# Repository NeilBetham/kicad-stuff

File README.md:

kicad-stuff
===========

This is my collection of KiCAD projects. I make no guarantee that they are good or will pass EMC. However most work to
my level of satisfaction.

I also have a lib from custom symbols and footprints but my hygine on labeling and naming is kinda shit so use at your
own risk there as well.

### Active Projects
- Davis Receiver - TM4C + CC1125, PoE powered wireless receiver for Davis Instruments ISS
- Sea LED - TM4C based, ethernet connected, DMX lighting controller for use with marine lighting
- Weir Controller - ESP32 + TI Phy, ethernet connected, pond pump / lighting controller
- Nixie Clock - ESP32 + RTC + Switcher, fully integrated IN-18 nixie clock
- USB C Ambient Light Sensor - Goal here is to build a small dongle to regulate display brightness based on ambient light

### Deep Freeze Projects
- Keyboard - TKL, many other good options at the moment so not much drive to finish this
- High Voltage Power Supply - Was just a test board to prove out the design for the nixie clock

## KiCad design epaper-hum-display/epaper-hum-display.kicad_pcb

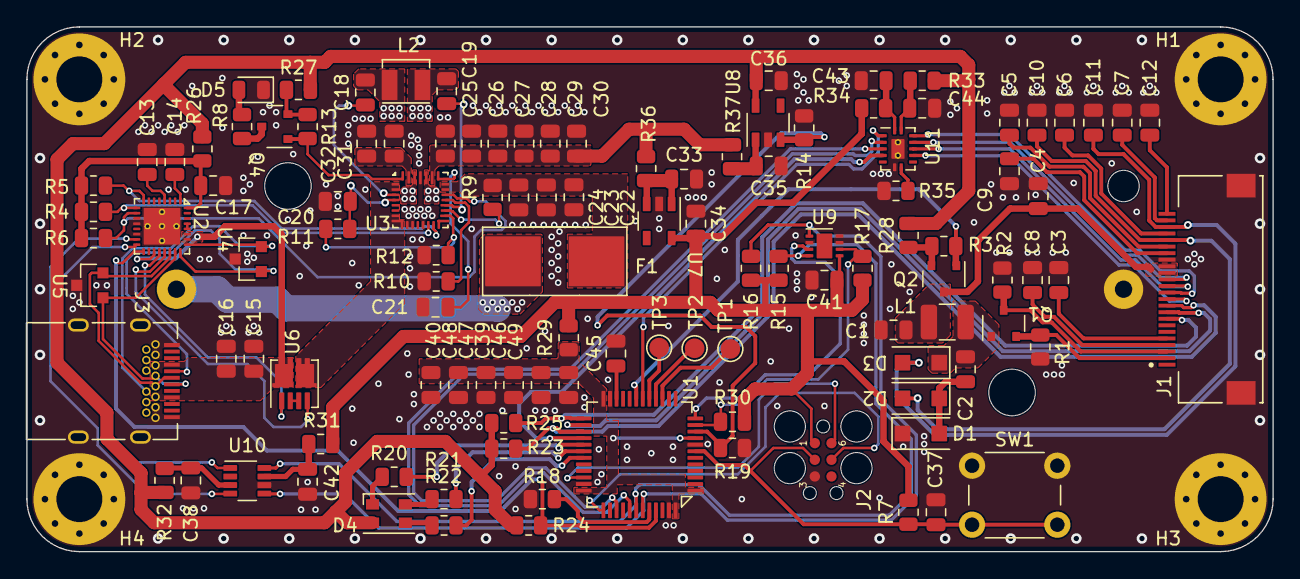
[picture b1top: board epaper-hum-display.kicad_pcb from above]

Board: 4 copper layers, 95.0 x 40.0 mm, 120 parts (1 on the bottom side), 93 nets.

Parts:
BT1: Battery_Cell; KEYSTONE-1043
C1, C2, C9: 4.7uF 50V; C_0805_2012Metric
C3, C5, C6, C7, C8, C10, C11, C12: 1uF 16V; C_0805_2012Metric
C4: 0.1 uF 16V; C_0805_2012Metric
C13, C14, C17, C23, C24, C26, C27, C28, C29, C30, C32, C34, C36, C40: 10uF 10V; C_0805_2012Metric
C15: 0.1uF 50V; C_0805_2012Metric
C16: 10uF 50V; C_0805_2012Metric
C18, C19: 0.047uF 25V; C_0805_2012Metric
C20: 4.7uF 25V; C_0805_2012Metric
C21: 1000pF 50V; C_0805_2012Metric
C22, C25, C31, C37, C38, C39, C41, C42, C43, C44, C46, C47, C48, C49: 0.1uF 10V; C_0805_2012Metric
C33, C35: 1uF 10V; C_0805_2012Metric
C45: 4.7uF 10V; C_0805_2012Metric
D1, D2, D3: MBR0530T1G; SOD-123W
D4: LED_RABG; LED_Cree-PLCC4_3.2x2.8mm_CCW
D5: BLUE; LED_0805_2012Metric
F1: Fuse; 01550900M
H1, H2, H3, H4: MountingHole_Pad; MountingHole_3.5mm_Pad_Via
J1: F31L-1A7H1-11024
J2: TC2030-SWD; TC2030-IDC-FP
J3: USB_C_Receptacle; Wurth_632723300011
L1: NLCV32T-680K-EF; L_1210_3225Metric
L2: SRP0315-1R0K; SRP0315
Q1: Si1308EDL; SOT-23-3
Q2, Q4: PMV65XP,215; SOT-23-3
R1, R3: 10K; R_0805_2012Metric
R2: 3; R_0805_2012Metric
R4, R5, R6, R15, R16, R17: 2.2k; R_0805_2012Metric
R7, R13, R14, R18, R19, R23, R24, R25, R30: 10k; R_0805_2012Metric
R8, R20, R21, R22: 500; R_0805_2012Metric
R9: 100; R_0805_2012Metric
R10: 3k 1%; R_0805_2012Metric
R11: 137k 1%; R_0805_2012Metric
R12: 2.2k 1%; R_0805_2012Metric
R26, R27, R28, R29, R31, R32, R33, R34, R35, R36, R37: 0; R_0805_2012Metric
SW1: B3F-1000; SW_PUSH_6mm
TP1, TP2, TP3: TestPoint; TestPoint_Pad_D1.5mm
U1: STM32U575CIT6Q; LQFP-48
U2: TPS25750S; VFQFN-32
U3: BQ25798; VFQFN-29
U4, U5: CDSOT23-0502B; SOT23-3L
U6: SISF00DN; PowerPAK 1212-8SCD Dual
U7: TPS7A2018PDBVR; SOT23-5
U8: TPS7A2033PDBVR; SOT23-5
U9: HDC3022; WSON-8
U10: TCA9416DDF; SOT-23-8
U11: TXU0104BQA; WQFN-14

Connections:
+1V8: C34.1, C41.1, J2.1 (VCC), R7.1, R15.1, R16.1, R17.1, R29.1, R30.1, R31.2, R34.2, U7.5 (OUT), U9.5 (VDD)
+3V3: C36.1, D4.2 (A), R23.1, R24.1, R25.1, R26.2, R27.1, R28.2, R32.1, R33.1, U8.5 (OUT)
/3V3_EN: R14.2, R19.1, U1.10 (PA0), U8.3 (EN)
/BATT_SCL: U2.16 (I2Cm_SCL), U10.1 (SCL_A)
/BATT_SDA: U2.15 (I2Cm_SDA), U10.4 (SDA_A)
/Battery/BQ_I2C_SCL: R4.2, U2.9 (I2Cs_SCL), U3.14 (SCL)
/Battery/BQ_I2C_SDA: R5.2, U2.8 (I2Cs_SDA), U3.15 (SDA)
/Battery/CC1: J3.A5 (CC1), U2.24 (CC1), U4.1
/Battery/CC2: J3.B5 (CC2), U2.25 (CC2), U4.2
/Battery/PD_CTRLR_3V3: C17.2, R4.1, R5.1, R6.1, R26.1, U2.32 (VIN_3V3)
/Battery/REGN: C20.1, R11.2, U3.5 (REGN)
/Battery/USB_N: J3.A7 (D-), J3.B7 (D-), U2.23 (GPIO5/USB_N), U5.1
/Battery/USB_P: J3.A6 (D+), J3.B6 (D+), U2.22 (GPIO4/USB_P), U5.2
/Battery/VBUS: C15.2, C16.2, J3.A4 (VBUS), J3.A9 (VBUS), J3.B4 (VBUS), J3.B9 (VBUS), U2.19 (VSYS), U2.26 (VBUS), U2.27 (VBUS), U6.7 (S1), U6.8 (S1)
/Battery/VSYS: C25.1, C26.1, C27.1, C28.1, C29.1, C30.1, R36.2, R37.2, U3.25 (SYS)
/Battery/~BQ_I2C_IRQ: R6.2, U2.10 (~I2Cs_IRQ), U3.21 (~INT)
/CDSTOP: TP2.1, U1.16 (PA6)
/CSLEEP: TP1.1, U1.15 (PA5)
/DISPLAY_BUSY: J1.9 (BUSY), U1.26 (PB13)
/DISPLAY_BUS_SEL: J1.8 (BS), R25.2, U1.25 (PB12)
/DISPLAY_CS: U1.18 (PB0), U11.2 (A1)
/DISPLAY_CS_S: J1.12 (CS), U11.13 (B1Y)
/DISPLAY_DATA_COMM_CTL: U1.28 (PB15), U11.5 (A4)
/DISPLAY_DATA_COMM_CTL_S: J1.11 (D/C), U11.10 (B4Y)
/DISPLAY_EN: Q2.1 (G), R3.1, U1.19 (PB1)
/DISPLAY_LVL_OE: R35.2, U11.8 (OE)
/DISPLAY_MOSI: U1.41 (PB5), U11.4 (A3)
/DISPLAY_MOSI_S: J1.14 (SDI), U11.12 (B2Y)
/DISPLAY_RESET: J1.10 (RST), R23.2, U1.27 (PB14)
/DISPLAY_SCLK: U1.39 (PB3), U11.3 (A2)
/DISPLAY_SCLK_S: J1.13 (SCLK), U11.11 (B3Y)
/E-Paper Display/EPAPER_3V3: C1.1, C4.1, J1.15 (VDDIO), J1.16 (VCI), L1.1, Q2.3 (D)
/E-Paper Display/GDR: J1.2 (GDR), Q1.2 (G), R1.2
/E-Paper Display/PREVGH: C10.1, D2.2 (A), J1.20 (VSH)
/E-Paper Display/PREVGL: C11.1, D3.2 (A), J1.22 (VSL)
/E-Paper Display/RESE: J1.3 (RESE), Q1.3 (S), R2.1
/HUM_ALERT: U1.12 (PA2), U9.3 (ALERT)
/HUM_RESET: R17.2, R30.2, U1.11 (PA1), U9.6 (~RESET)
/I2C_SCL: R15.2, U1.42 (PB6), U9.4 (SCL), U10.8 (SCL_B)
/I2C_SDA: R16.2, U1.43 (PB7), U9.1 (SDA), U10.5 (SDA_B)
/IND_B: R22.2, U1.31 (PA10)
/IND_G: R21.2, U1.30 (PA9)
/IND_R: R20.2, U1.29 (PA8)
/SRDSTOP: TP3.1, U1.17 (PA7)
/SWCLK: J2.5 (SWDCLK), U1.37 (PA14)
/SWDIO: J2.6 (SWDIO), U1.34 (PA13)
/nRESET: C37.1, J2.2 (nRESET), R7.2, SW1.2, U1.7 (NRST)
/~BATT_IRQ: R24.2, U1.45 (PB8), U2.17 (~I2Cm_IRQ)
GND: BT1.2 (-), C1.2, C3.2, C4.2, C5.2, C6.2, C7.2, C8.2, C9.2, C10.2, C11.2, C12.2, C13.2, C14.2, C15.1, C16.1, C17.1, C20.2, C21.2, C22.2, C23.2, C24.2, C25.2, C26.2, C27.2, C28.2, C29.2, C30.2, C31.2, C32.2, C33.2, C34.2, C35.2, C36.2, C37.2, C38.2, C39.2, C40.2, C41.2, C42.2, C43.2, C44.2, C45.1, C46.2, C47.2, C48.2, C49.2, D1.1 (K), D5.1 (K), H1.1, H2.1, H3.1, H4.1, J1.17 (VSS), J1.GND, J2.3 (GND), J3.A1 (GND), J3.A12 (GND), J3.B1 (GND), J3.B12 (GND), J3.S1 (SHIELD), R1.1, R2.2, R10.2, R12.1, R14.1, R18.2, R19.2, R35.1, SW1.1, U1.8 (VSSA), U1.23 (VSS), U1.35 (VSS), U1.47 (VSS), U2.11 (GND), U2.12 (GND), U2.14 (GND), U2.33 (GND), U3.10 (ACDRV2), U3.11 (ACDRV1), U3.13 (~CE), U3.27 (GND), U4.3, U5.3, U7.2 (GND), U8.2 (GND), U9.2 (ADDR), U9.7 (ADDR1), U9.8 (GND), U10.6 (GND), U11.7 (GND), U11.15 (GND)
unnamed: BT1.1 (+), F1.2
unnamed: C22.1, C23.1, C24.1, F1.1, R9.1, U3.22 (BAT), U3.23 (BAT)
unnamed: C2.1, D1.2 (A), D2.1 (K)
unnamed: C2.2, D3.1 (K), L1.2, Q1.1 (D)
unnamed: D4.3 (BK), R22.1
unnamed: D4.4 (GK), R21.1
unnamed: D4.1 (RK), R20.1
unnamed: D5.2 (A), R8.2
unnamed: C6.1, J1.21 (PREVGH)
unnamed: C7.1, J1.23 (PREVGL)
unnamed: C12.1, J1.24 (VCOM)
unnamed: C9.1, J1.18 (VDD)
unnamed: C3.1, J1.5 (VGH)
unnamed: C8.1, J1.4 (VGL)
unnamed: C5.1, J1.19 (VPP)
unnamed: Q2.2 (S), R3.2, R28.1
unnamed: Q4.3 (D), R8.1
unnamed: Q4.1 (G), R13.2, U3.1 (STAT)
unnamed: Q4.2 (S), R13.1, R27.2
unnamed: R18.1, U1.44 (PH3/BOOT0)
unnamed: C39.1, C40.1, C46.1, C47.1, C48.1, C49.1, R29.2, U1.1 (VBAT), U1.9 (VDDA), U1.24 (VDD), U1.36 (VDD), U1.48 (VDD)
unnamed: C45.2, U1.22 (VCAP)
unnamed: U2.21 (GATE_VBUS), U6.4 (G2)
unnamed: U2.20 (GATE_VSYS), U6.1 (G1)
unnamed: C13.1, U2.4 (LDO_1V5)
unnamed: C14.1, U2.1 (LDO_3V3)
unnamed: U2.28 (PP5V), U2.29 (PP5V)
unnamed: R9.2, U3.18 (BATP)
unnamed: C18.1, U3.4 (BTST1)
unnamed: C19.1, U3.19 (BTST2)
unnamed: R11.1, R12.2, U3.17 (ILIM_HIZ)
unnamed: C31.1, C32.1, U3.29 (PMID)
unnamed: R10.1, U3.20 (PROG)
unnamed: C21.1, U3.24 (SDRV)
unnamed: C18.2, L2.2, U3.28 (SW1)
unnamed: C19.2, L2.1, U3.26 (SW2)
unnamed: U3.2 (VBUS), U3.3 (VBUS), U3.8 (VAC2), U3.9 (VAC1), U6.5 (S2), U6.6 (S2)
unnamed: U6.2 (D), U6.3 (D)
unnamed: C33.1, R36.1, U7.1 (IN), U7.3 (EN)
unnamed: C35.1, R37.1, U8.1 (IN)
unnamed: C38.1, R32.2, U10.3 (VCCA)
unnamed: C42.1, R31.1, U10.7 (VCCB)
unnamed: C43.1, R34.1, U11.1 (VCCA)
unnamed: C44.1, R33.2, U11.14 (VCCB)

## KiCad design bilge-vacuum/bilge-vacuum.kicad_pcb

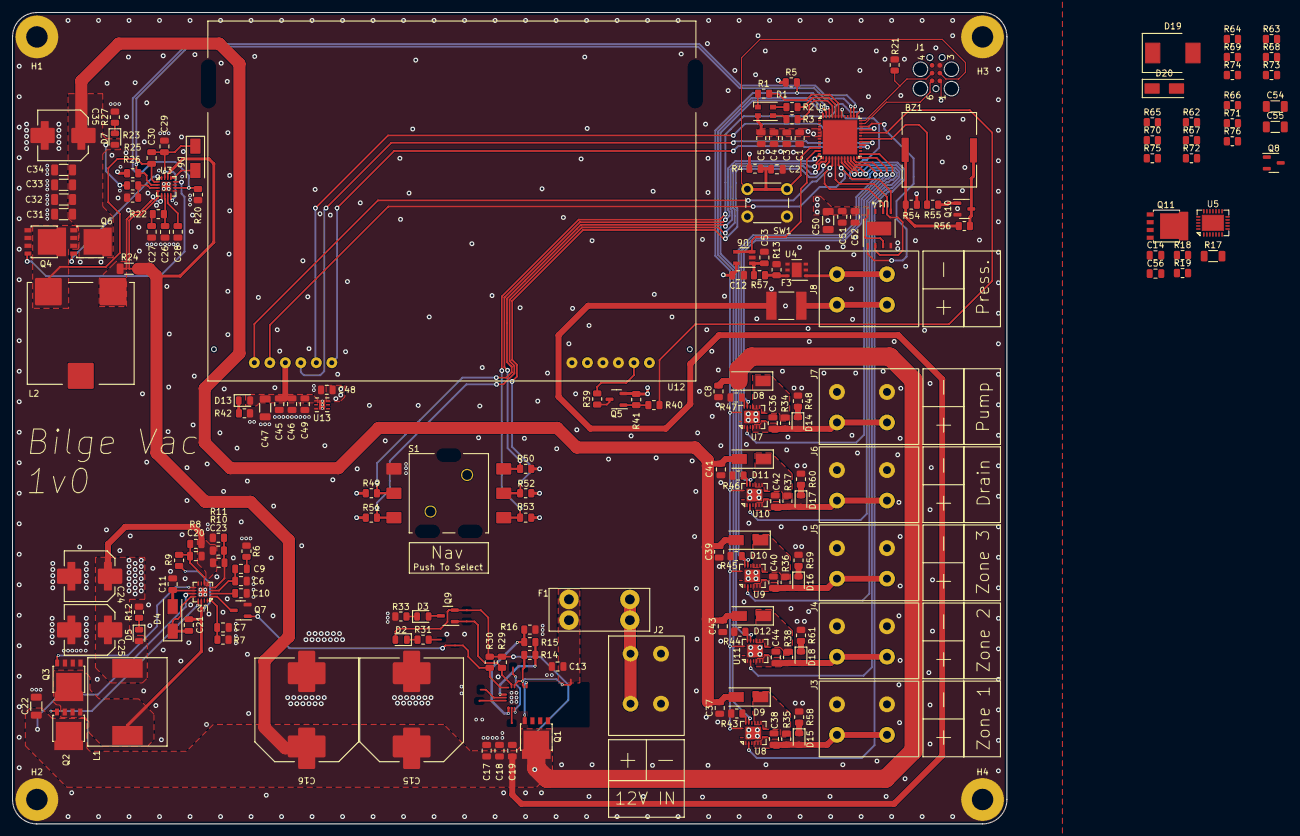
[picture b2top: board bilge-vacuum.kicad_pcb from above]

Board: 4 copper layers, 163.0 x 133.0 mm, 194 parts (0 on the bottom side), 113 nets.

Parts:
BZ1: PKLCS1212E40A1-R1
C1, C2, C3, C7, C8, C10, C12, C13, C14, C21, C28, C30, C36, C37, C38, C39, C40, C41, C42, C43, C44, C45, C52, C53, C56: 0.1uF 50V; C_0805_2012Metric
C4, C46, C48, C49, C51: 1uF 25V; C_0805_2012Metric
C5, C11, C17, C18, C19, C29: 4.7uF 50V; C_0805_2012Metric
C6: 330pF 25V; C_0805_2012Metric
C9: 2200pF 25V; C_0805_2012Metric
C15, C16: EEE-FK1H102AV; Panasonic - J - Vibe
C20: 0.047uF 25V; C_0805_2012Metric
C22, C31, C32, C33, C34, C47, C50, C54, C55: 10uF 50V; C_1206_3216Metric
C23: 47pF 10V; C_0805_2012Metric
C24, C25: EEE-FK1A331AV; Panasonic - F - Vibe
C26: 220pF 25V; C_0805_2012Metric
C27: 15000pF 25V; C_0805_2012Metric
C35: EEEFT1H221GV; Panasonic - F - Vibe
D1: LED_RABG; LED_Cree-PLCC4_3.2x2.8mm_CCW
D2, D5, D7, D13, D14, D15, D16, D17, D18: GREEN; LED_0805_2012Metric
D3: RED; LED_0805_2012Metric
D4, D6, D8, D9, D10, D11, D12, D20: B260AQ-13-F; SMA
D19: 5.0SMDJ18CA; DO-214AB
F1: Fuse; Keystone-3568
F3: Polyfuse; SMD_2016
H1, H2, H3, H4: MountingHole_Pad; MountingHole_3.5mm_Pad
J1: TC2030-SWD; TC2030-IDC-FP
J2, J3, J4, J5, J6, J7, J8: Screw_Terminal_01x02; 2604-1102
L1: SRP1265A-R68M; SRP1265A
L2: B82559B6682A016; TDK-ERU-16
Q1, Q2, Q3, Q4, Q6, Q11: PSMN014-80YL; LFPAK56
Q5: PMV65XP,215; SOT-23-3
Q7, Q10: Q_NMOS_GSD; SOT-23-3
Q8, Q9: Q_PMOS_GSD; SOT-23-3
R1, R2, R3, R12, R42: 499; R_0805_2012Metric
R4, R5, R20, R23, R27, R29, R30, R41, R48, R49, R50, R51, R52, R53, R58, R59, R60, R61, R62, R63, R64, R65, R66, R67, R68, R69, R70, R71, R72, R73, R74, R75, R76: 10k 1%; R_0805_2012Metric
R6, R18, R34, R35, R36, R37, R38: 15k; R_0805_2012Metric
R7: 82.5k; R_0805_2012Metric
R8: 30.1k; R_0805_2012Metric
R9: 3.01k; R_0805_2012Metric
R10: 154k 1%; R_0805_2012Metric
R11: 48.7k 1%; R_0805_2012Metric
R13: 100 1%; R_0805_2012Metric
R14: 21.5k 1%; R_0805_2012Metric
R15: 1.1k 1%; R_0805_2012Metric
R16: 2k 1%; R_0805_2012Metric
R17: 3m 1% 1/2W; R_1206_3216Metric
R19: 2k; R_0805_2012Metric
R21: NP; R_0805_2012Metric
R22: 8.87k 1%; R_0805_2012Metric
R24: 8m 1%; R_1206_3216Metric
R25: 232k 1%; R_0805_2012Metric
R26: 12.1k 1%; R_0805_2012Metric
R31, R33, R43, R44, R45, R46: 5k 1%; R_0805_2012Metric
R39, R57: 0; R_0805_2012Metric
R40, R54, R55: 10; R_0805_2012Metric
R47: 1.2k 1%; R_0805_2012Metric
R56: 1k; R_0805_2012Metric
S1: JS5208
SW1: B3F-1000; SW_PUSH_6mm
U1: STM32G0B1CEU6; UFQFPN-48
U2: LTC3851; QFN-16
U3: LTC3786; QFN-16
U4: MAX14626; TDFN-6
U5: LTC4229; WFQFN-24
U6: LMV321; SOT23-5
U7, U8, U9, U10, U11: TPS27S100A; WQFN-16
U12: NHD-C12864A1Z-FSW-FBW-HTT
U13: ADP151; CP_6_3_ADI
U14: FM25V20A; WDFN-8

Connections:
+3V0: C45.1, C46.1, C47.1, C49.1, D13.2 (A), U12.3 (VDD), U13.1 (VOUT)
+3V3: C1.1, C3.1, C4.1, C5.1, C12.2, C20.2, C23.2, C24.1, C25.1, C48.1, C50.1, C51.1, C52.1, D1.2 (A), D5.2 (A), J1.1 (VCC), L1.2, Q5.2 (S), R4.1, R5.1, R8.2, R10.1, R23.2, R41.2, R49.1, R50.1, R51.1, R52.1, R53.1, R54.1, R72.2, R73.2, R74.2, R75.2, R76.2, U1.4 (VBAT), U1.5 (VREF+), U1.6 (VDD/VDDA), U2.5 (SENSE_N), U6.5 (V+), U13.6 (VIN), U14.3 (~WP), U14.8 (VDD)
+12V: C8.2, C15.1, C16.1, C17.1, C18.1, C19.1, C22.1, C54.1, C55.1, D8.2 (A), D20.1 (K), F3.1, Q1.1 (S), Q1.2 (S), Q1.3 (S), Q2.5 (D), Q8.2 (S), Q9.2 (S), R18.1, R24.1, R29.2, R30.2, U2.11 (VIN), U3.4 (SENSE+), U3.14 (VBIAS), U5.21 (OUT)
+24V: C31.1, C32.1, C33.1, C34.1, C35.1, C37.2, C39.2, C41.2, C43.2, D7.2 (A), D9.2 (A), D10.2 (A), D11.2 (A), D12.2 (A), Q6.5 (D), R25.1
/Display/BL_ENABLE: R40.1, U1.32 (PA10)
/Display/CS: U1.28 (PA8), U12.6 (~CS)
/Display/MOSI: U1.18 (PA7), U12.2 (SI), U14.5 (SI)
/Display/REG: U1.29 (PA9), U12.4 (A0)
/Display/RESET: U1.33 (PA11), U12.5 (~RESET)
/Display/SCLK: U1.16 (PA5), U12.1 (SCL), U14.6 (SCLK)
/FRAM/CS: U1.34 (PA12), U14.1 (~CS)
/FRAM/MISO: U1.17 (PA6), U14.2 (SO)
/Main uC/24V_ENABLE: R20.2, U1.38 (PD0), U3.10 (RUN)
/Main uC/24V_PGOOD: R23.1, U1.39 (PD1), U3.2 (PGOOD)
/Main uC/BUZZER_DRIVE: R55.1, U1.30 (PC6)
/Main uC/DISPLAY_3V0_ENABLE: U1.31 (PC7), U13.4 (EN)
/Main uC/IND_B: R3.2, U1.45 (PB6)
/Main uC/IND_G: R2.2, U1.44 (PB5)
/Main uC/IND_R: R1.2, U1.43 (PB4)
/Main uC/NAV_A: R50.2, S1.4 (A), U1.12 (PA1)
/Main uC/NAV_B: R49.2, S1.2 (B), U1.13 (PA2)
/Main uC/NAV_C: R53.2, S1.6 (C), U1.37 (PA15)
/Main uC/NAV_D: R52.2, S1.5 (D), U1.15 (PA4)
/Main uC/NAV_SEL: R51.2, S1.3 (SEL), U1.14 (PA3)
/Main uC/PRESSURE_ADC: U1.11 (PA0), U6.3 (-), U6.4
/Main uC/SWDCLK: J1.5 (SWDCLK), R21.1, U1.36 (PA14-BOOT0)
/Main uC/SWDIO: J1.6 (SWDIO), U1.35 (PA13)
/Main uC/nRESET: C2.1, J1.2 (nRESET), R4.2, SW1.2, U1.10 (PF2-NRST)
/Output Control/PUMP_DIAG: R62.1, U1.24 (PB12), U7.14 (DIAG_EN)
/Output Control/PUMP_EN: R67.1, U1.25 (PB13), U7.3 (EN)
/Output Control/PUMP_FLT: R5.2, R72.1, R73.1, R74.1, R75.1, R76.1, U1.46 (PB7), U7.16 (~FLT), U8.16 (~FLT), U9.16 (~FLT), U10.16 (~FLT), U11.16 (~FLT)
/Output Control/Pump Switch/CURRENT_LIMIT: R47.1, U7.15 (ILIM)
/Output Control/Pump Switch/OUT: C36.2, D14.2 (A), J7.1, R34.2, U7.5 (OUT), U7.6 (OUT), U7.7 (OUT), U7.8 (OUT)
/Output Control/SOL_1_DIAG: R63.1, U1.47 (PB8), U8.14 (DIAG_EN)
/Output Control/SOL_1_EN: R68.1, U1.19 (PB0), U8.3 (EN)
/Output Control/SOL_2_DIAG: R66.1, U1.48 (PB9), U11.14 (DIAG_EN)
/Output Control/SOL_2_EN: R71.1, U1.20 (PB1), U11.3 (EN)
/Output Control/SOL_3_DIAG: R64.1, U1.22 (PB10), U9.14 (DIAG_EN)
/Output Control/SOL_3_EN: R69.1, U1.21 (PB2), U9.3 (EN)
/Output Control/SOL_4_DIAG: R65.1, U1.23 (PB11), U10.14 (DIAG_EN)
/Output Control/SOL_4_EN: R70.1, U1.42 (PB3), U10.3 (EN)
/Output Control/Solenoid 1/CURRENT_LIMIT: R43.2, U8.15 (ILIM)
/Output Control/Solenoid 1/OUT: C38.2, D15.2 (A), J3.1, R35.2, U8.5 (OUT), U8.6 (OUT), U8.7 (OUT), U8.8 (OUT)
/Output Control/Solenoid 2/CURRENT_LIMIT: R44.2, U11.15 (ILIM)
/Output Control/Solenoid 2/OUT: C44.2, D18.2 (A), J4.1, R38.2, U11.5 (OUT), U11.6 (OUT), U11.7 (OUT), U11.8 (OUT)
/Output Control/Solenoid 3/CURRENT_LIMIT: R45.2, U9.15 (ILIM)
/Output Control/Solenoid 3/OUT: C40.2, D16.2 (A), J5.1, R36.2, U9.5 (OUT), U9.6 (OUT), U9.7 (OUT), U9.8 (OUT)
/Output Control/Solenoid 4/CURRENT_LIMIT: R46.2, U10.15 (ILIM)
/Output Control/Solenoid 4/OUT: C42.2, D17.2 (A), J6.1, R37.2, U10.5 (OUT), U10.6 (OUT), U10.7 (OUT), U10.8 (OUT)
/Power/3.3V Buck/BUCK_BG: Q3.4 (G), U2.9 (BG)
/Power/3.3V Buck/BUCK_TG: Q2.4 (G), U2.13 (TG)
/Power/3V3_ENABLE: Q7.3 (D), U2.1 (RUN)
/Power/24V Boost/24V_INTVCC: C29.2, D6.2 (A), U3.8 (PLLIN/MODE), U3.13 (INTVcc)
/Power/24V Boost/BOOST_BG: Q4.4 (G), U3.12 (BG)
/Power/24V Boost/BOOST_TG: Q6.4 (G), U3.16 (TG)
/Power/Input Protection/DIODE_GATE: Q11.4 (G), U5.24 (DGATE)
/Power/Input Protection/FOLDBACK_SENSE: R18.2, R19.1, U5.20 (FB)
/Power/Input Protection/HOTSWAP_GATE: Q1.4 (G), U5.22 (HGATE)
/Power/Input Protection/OVERVOLT_SENSE: R15.1, R16.2, U5.13 (OV)
/Power/Input Protection/SENSE_N: Q1.5 (D), Q11.5 (D), R17.1, R17.2, U5.2 (SENSE_N), U5.3 (SENSE_P), U5.5 (DSNS)
/Power/Input Protection/UNDERVOLT_SENSE: R14.1, R15.2, U5.12 (UV)
/Power/Input Protection/VIN: C13.1, D19.2 (A2), F1.1, F1.2, J2.1, Q11.1 (S), Q11.2 (S), Q11.3 (S), R14.2, U5.1 (DSRC), U5.4 (IN)
/Power/Input Protection/~FAULT: Q9.1 (G), R29.1, U5.18 (~FAULT)
/Power/Input Protection/~PGOOD: Q7.1 (G), Q8.1 (G), R30.1, U5.19 (~PWRGD)
GND: C1.2, C2.2, C3.2, C4.2, C5.2, C6.1, C7.1, C8.1, C10.1, C11.2, C12.1, C13.2, C14.2, C15.2, C16.2, C17.2, C18.2, C19.2, C22.2, C24.2, C25.2, C26.1, C27.1, C28.1, C29.1, C31.2, C32.2, C33.2, C34.2, C35.2, C36.1, C37.1, C38.1, C39.1, C40.1, C41.1, C42.1, C43.1, C44.1, C45.2, C46.2, C47.2, C48.2, C49.2, C50.2, C51.2, C52.2, C53.1, C54.2, C55.2, C56.2, D19.1 (A1), D20.2 (A), H1.1, H2.1, H3.1, H4.1, J1.3 (GND), J2.2, J3.2, J4.2, J5.2, J6.2, J7.2, Q3.1 (S), Q3.2 (S), Q3.3 (S), Q4.1 (S), Q4.2 (S), Q4.3 (S), Q7.2 (S), Q10.2 (S), R6.1, R7.1, R11.2, R12.2, R13.1, R16.1, R19.2, R20.1, R21.2, R26.1, R27.2, R31.2, R33.2, R42.2, R43.1, R44.1, R45.1, R46.1, R47.2, R48.2, R58.2, R59.2, R60.2, R61.2, R62.2, R63.2, R64.2, R65.2, R66.2, R67.2, R68.2, R69.2, R70.2, R71.2, S1.1 (COM), SW1.1, U1.7 (VSS/VSSA), U1.49 (VSS), U2.8 (GND), U2.17 (GND), U3.9 (FREQ), U3.11 (GND), U3.17 (GND), U4.2 (GND), U4.3 (GND), U4.4 (GND), U4.5 (GND), U4.7 (GND), U5.7 (GND), U5.11 (~EN), U5.14 (DCFG), U5.15 (DOFF), U5.25 (GND), U6.2 (V-), U7.2 (GND), U7.17 (GND), U8.2 (GND), U8.17 (GND), U9.2 (GND), U9.17 (GND), U10.2 (GND), U10.17 (GND), U11.2 (GND), U11.17 (GND), U12.7 (VSS), U12.9 (HEATER_GND), U12.10 (LED_GND), U13.3 (GND), U13.7 (GND), U14.4 (VSS)
unnamed: BZ1.2 (+), Q10.3 (D), R56.1
unnamed: BZ1.1 (-), R54.2, R56.2
unnamed: C9.1, R6.2
unnamed: C27.2, R22.1
unnamed: D1.3 (BK), R3.1
unnamed: D1.4 (GK), R2.1
unnamed: D1.1 (RK), R1.1
unnamed: D2.2 (A), Q8.3 (D)
unnamed: D2.1 (K), R31.1
unnamed: D3.2 (A), Q9.3 (D)
unnamed: D3.1 (K), R33.1
unnamed: C11.1, D4.2 (A), U2.10 (INTVCC)
unnamed: C21.1, D4.1 (K), U2.12 (BOOST)
unnamed: D5.1 (K), R12.1
unnamed: C30.1, D6.1 (K), U3.15 (BOOST)
unnamed: D7.1 (K), R27.1
unnamed: D8.1 (K), R34.1, U7.9 (IN), U7.10 (IN), U7.11 (IN), U7.12 (IN)
unnamed: D9.1 (K), R35.1, U8.9 (IN), U8.10 (IN), U8.11 (IN), U8.12 (IN)
unnamed: D10.1 (K), R36.1, U9.9 (IN), U9.10 (IN), U9.11 (IN), U9.12 (IN)
unnamed: D11.1 (K), R37.1, U10.9 (IN), U10.10 (IN), U10.11 (IN), U10.12 (IN)
unnamed: D12.1 (K), R38.1, U11.9 (IN), U11.10 (IN), U11.11 (IN), U11.12 (IN)
unnamed: D13.1 (K), R42.1
unnamed: D14.1 (K), R48.1
unnamed: D15.1 (K), R58.1
unnamed: D16.1 (K), R59.1
unnamed: D17.1 (K), R60.1
unnamed: D18.1 (K), R61.1
unnamed: F3.2, J8.1
unnamed: J8.2, U4.1 (IN)
unnamed: C21.2, L1.1, Q2.1 (S), Q2.2 (S), Q2.3 (S), Q3.5 (D), R9.1, U2.14 (SW)
unnamed: C30.2, L2.2, Q4.5 (D), Q6.1 (S), Q6.2 (S), Q6.3 (S), U3.1 (SW)
unnamed: Q5.3 (D), R39.2
unnamed: Q5.1 (G), R40.2, R41.1
unnamed: Q10.1 (G), R55.2
unnamed: C23.1, R10.2, R11.1, U2.4 (FB)
unnamed: C7.2, R7.2, U2.16 (FREQ/PLLFLTR)
unnamed: C6.2, C9.2, U2.3 (ITH)
unnamed: C20.1, R8.1, R9.2, U2.6 (SENSE_P)
unnamed: C10.2, U2.2 (TK/SS)
unnamed: C26.2, R22.2, U3.6 (ITH)
unnamed: L2.1, R24.2, U3.5 (SENSE-)
unnamed: C28.2, U3.7 (SS)
unnamed: R25.2, R26.2, U3.3 (VFB)
unnamed: R13.2, R57.2, U4.6 (OUT)
unnamed: C56.1, U5.6 (INTVcc), U5.8 (DTMR)
unnamed: C14.1, U5.10 (FTMR)
unnamed: C53.2, R57.1, U6.1 (+)
unnamed: R39.1, U12.11 (LED_3V3)

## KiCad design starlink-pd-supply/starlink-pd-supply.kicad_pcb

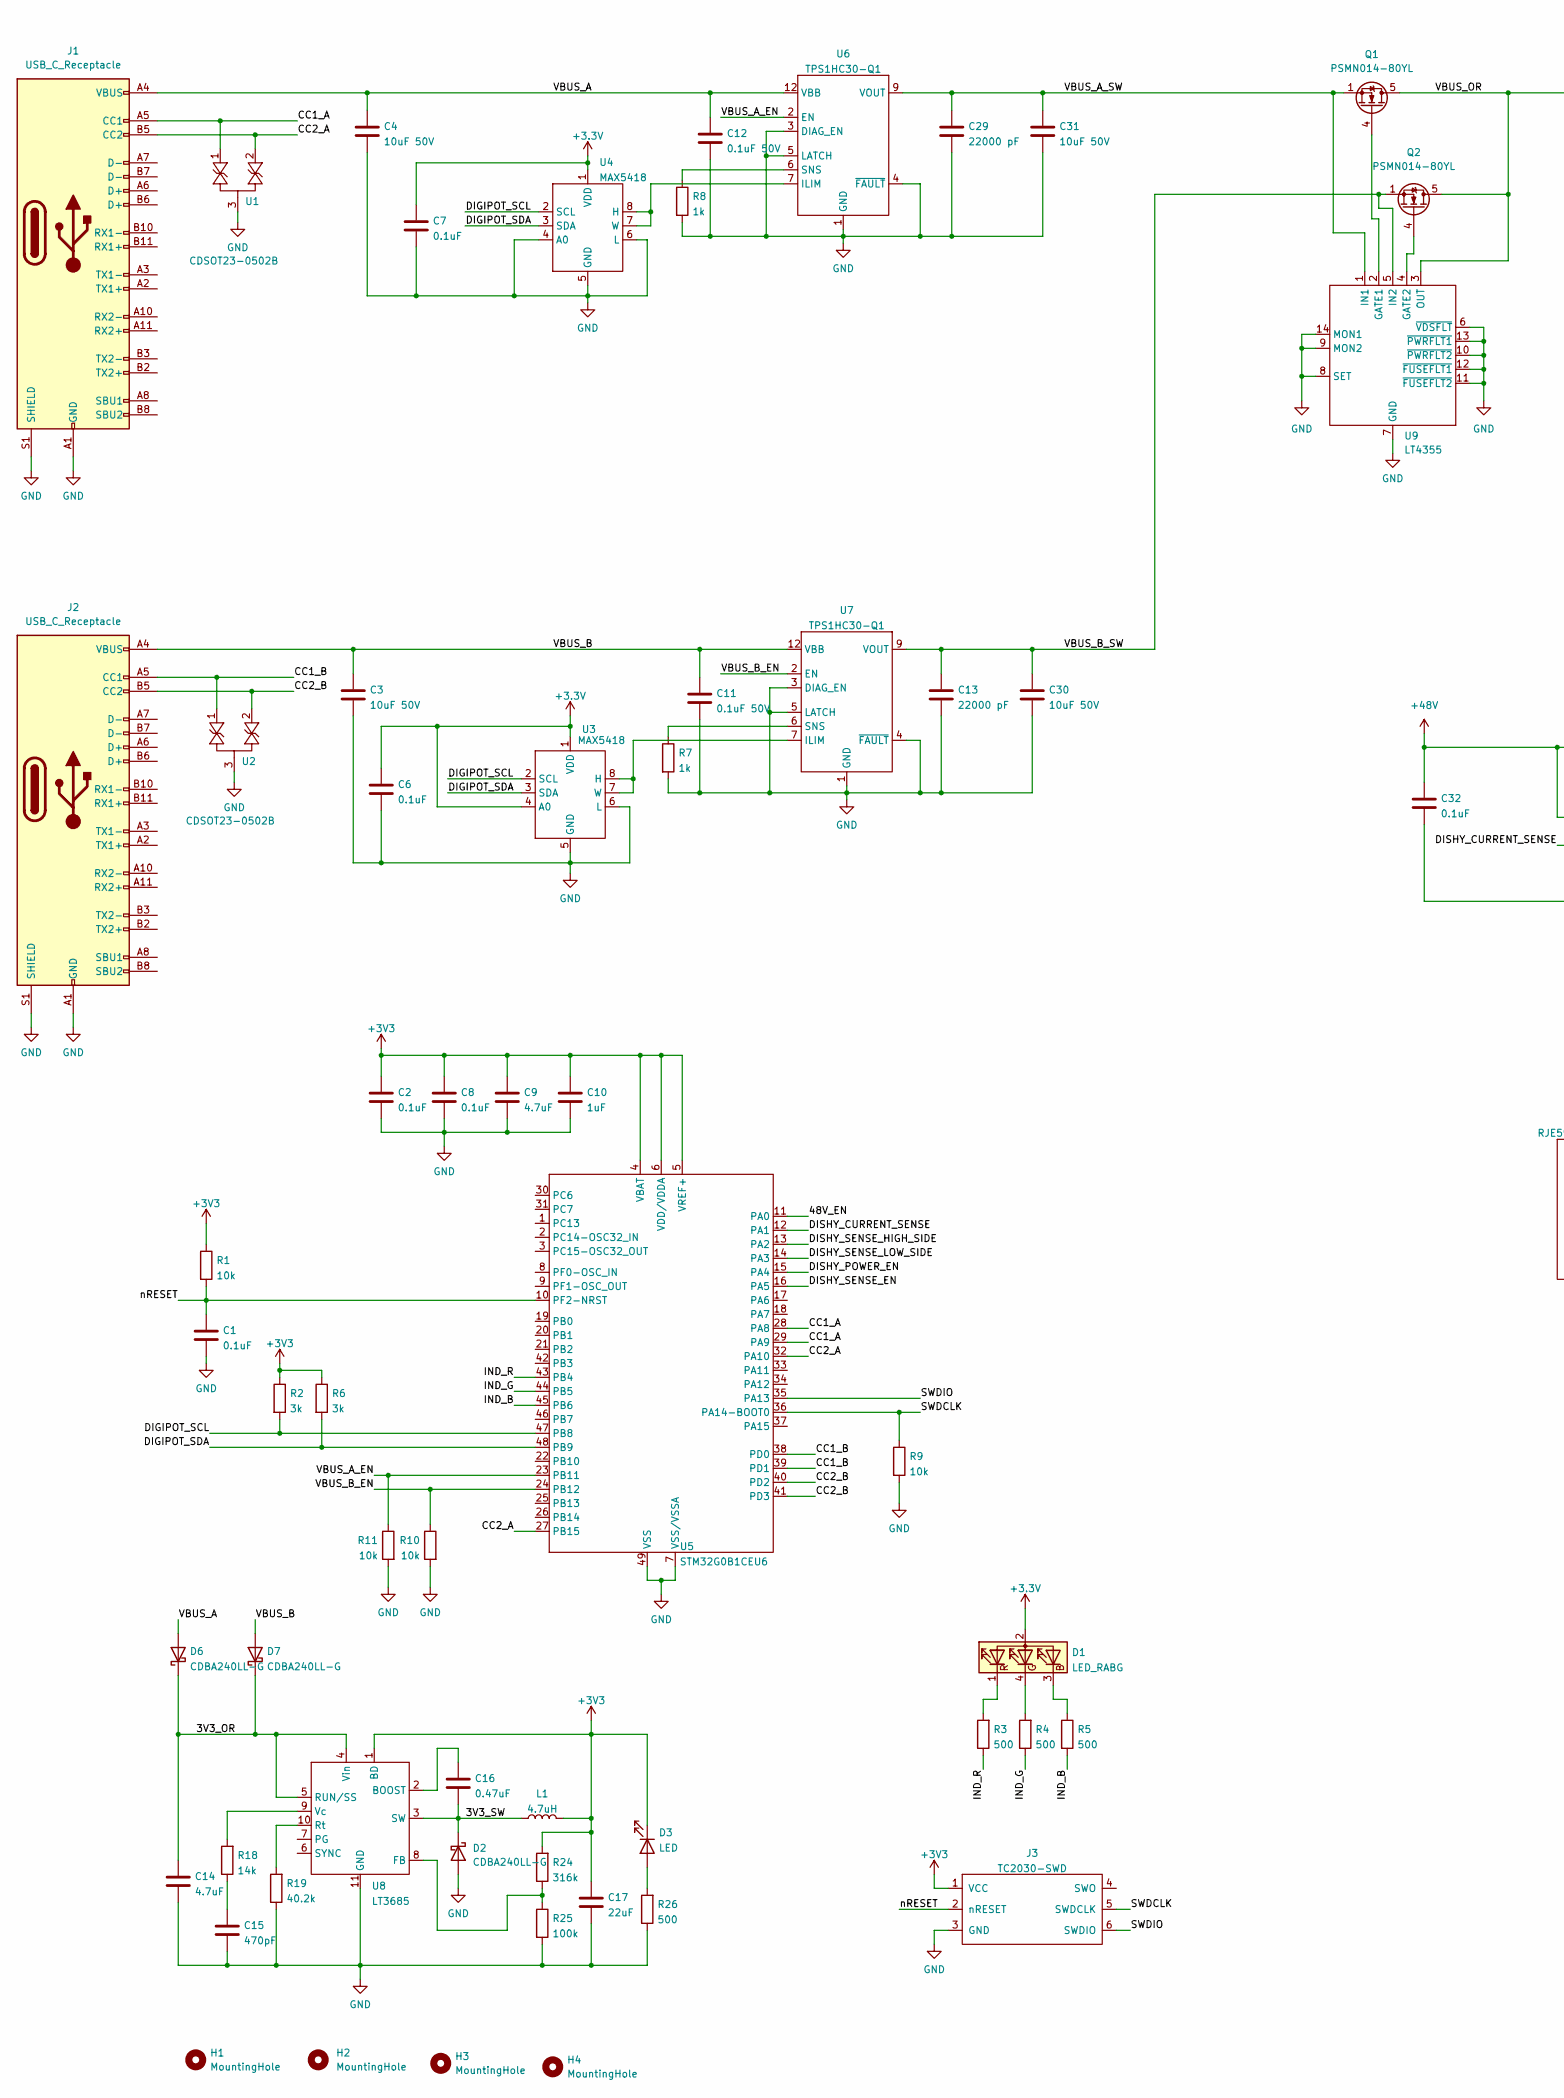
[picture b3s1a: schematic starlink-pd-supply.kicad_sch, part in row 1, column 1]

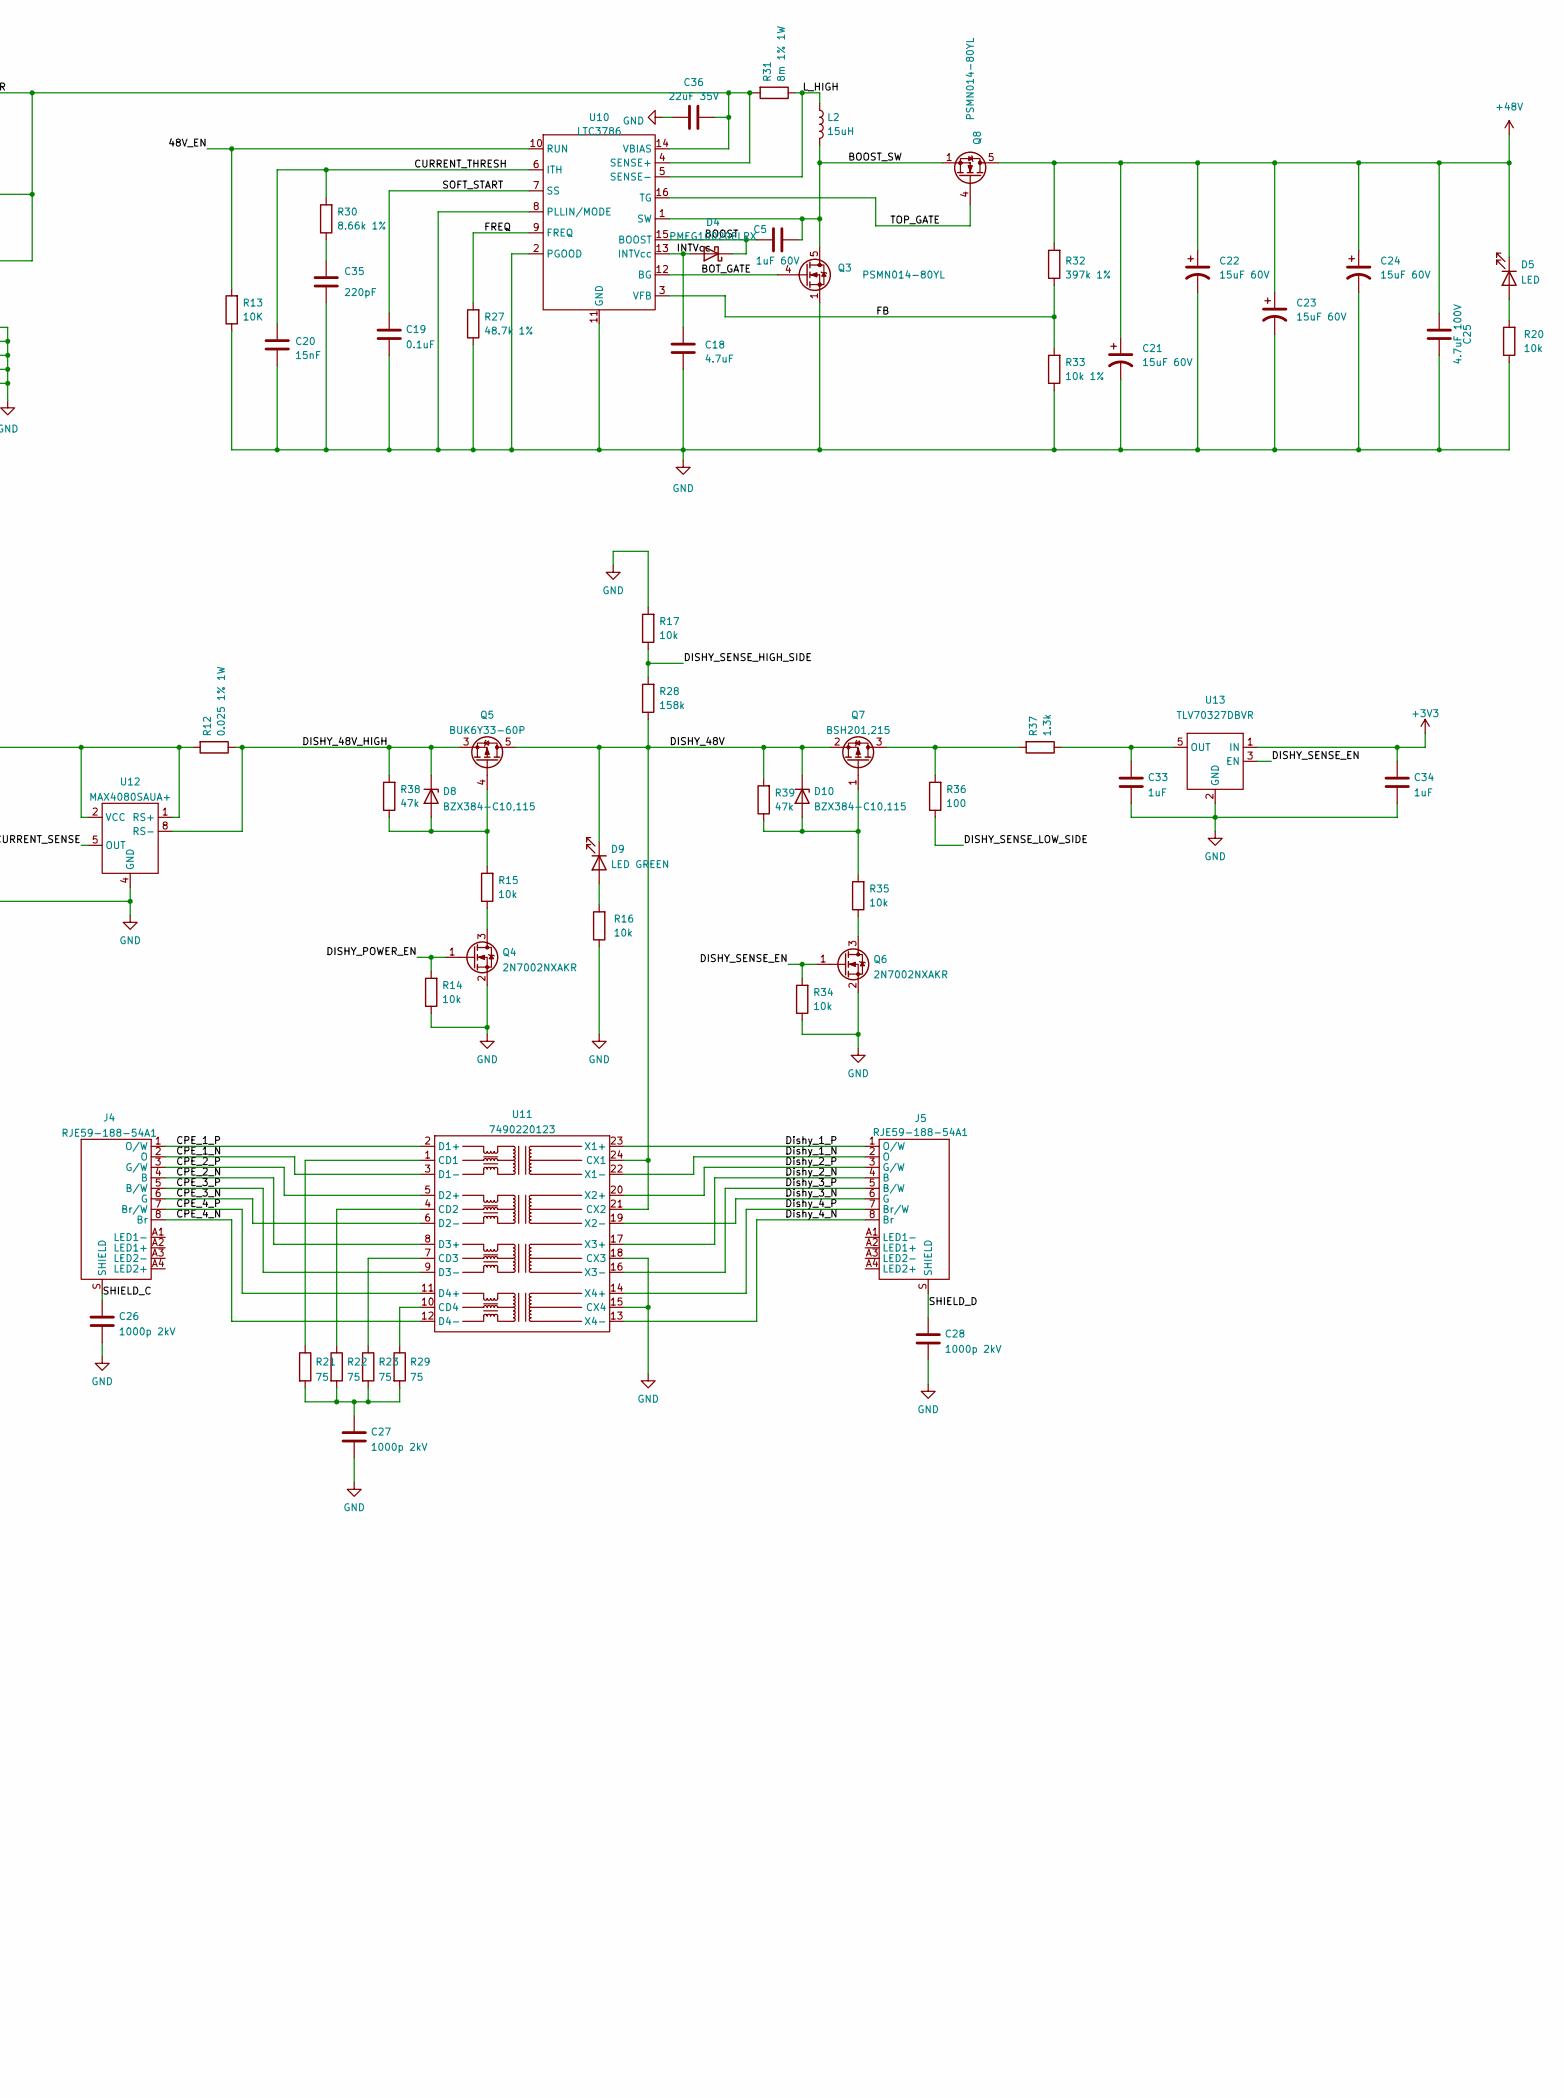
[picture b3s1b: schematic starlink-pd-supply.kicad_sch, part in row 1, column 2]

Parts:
C1, C2, C6, C7, C8, C19, C32: 0.1uF; C_0805_2012Metric
C3, C4, C30, C31: 10uF 50V; C_1210_3225Metric
C5: 1uF 60V; C_0805_2012Metric
C9, C14, C18: 4.7uF; C_0805_2012Metric
C10, C33, C34: 1uF; C_0805_2012Metric
C11, C12: 0.1uF 50V; C_0805_2012Metric
C13, C29: 22000 pF; C_0805_2012Metric
C15: 470pF; C_0805_2012Metric
C16: 0.47uF; C_0805_2012Metric
C17: 22uF; C_0805_2012Metric
C20: 15nF; C_0805_2012Metric
C21, C22, C23, C24: 15uF 60V; Panasonic-F8
C25: 4.7uF 100V; C_0805_2012Metric
C26, C27, C28: 1000p 2kV; C_1206_3216Metric
C35: 220pF; C_0805_2012Metric
C36: 22uF 35V; C_1206_3216Metric
D1: LED_RABG; LED_Cree-PLCC4_3.2x2.8mm_CCW
D2, D6, D7: CDBA240LL-G; SMA
D3, D5: LED; LED_0805_2012Metric
D4: PMEG10020ELRX; SOD-123W
D8, D10: BZX384-C10,115; SOD-323
D9: LED GREEN; LED_0805_2012Metric
H1, H2, H3, H4: MountingHole; MountingHole_4mm_Pad_Via
J1, J2: USB_C_Receptacle; Wurth_632723300011
J3: TC2030-SWD; TC2030-IDC-FP
J4, J5: RJE59-188-54A1
L1: 4.7uH; SRP0620
L2: 15uH; SRP1513CA
Q1, Q2, Q3, Q8: PSMN014-80YL; LFPAK56
Q4, Q6: 2N7002NXAKR; SOT-23
Q5: BUK6Y33-60P; LFPAK56
Q7: BSH201,215; SOT-23
R1, R9, R10, R11, R14, R15, R16, R17, R20, R34, R35: 10k; R_0805_2012Metric
R2, R6: 3k; R_0805_2012Metric
R3, R4, R5, R26: 500; R_0805_2012Metric
R7, R8: 1k; R_0805_2012Metric
R12: 0.025 1% 1W; R_1206_3216Metric
R13: 10K; R_0805_2012Metric
R18: 14k; R_0805_2012Metric
R19: 40.2k; R_0805_2012Metric
R21, R22, R23, R29: 75; R_0805_2012Metric
R24: 316k; R_0805_2012Metric
R25: 100k; R_0805_2012Metric
R27: 48.7k 1%; R_0805_2012Metric
R28: 158k; R_0805_2012Metric
R30: 8.66k 1%; R_0805_2012Metric
R31: 8m 1% 1W; R_1206_3216Metric
R32: 397k 1%; R_0805_2012Metric
R33: 10k 1%; R_0805_2012Metric
R36: 100; R_0805_2012Metric
R37: 1.3k; R_0805_2012Metric
R38, R39: 47k; R_0805_2012Metric
U1, U2: CDSOT23-0502B; SOT23-3L
U3, U4: MAX5418; TDFN-8
U5: STM32G0B1CEU6; UFQFPN-48
U6, U7: TPS1HC30-Q1; TSSOP-14
U8: LT3685; DFN-10
U9: LT4355; DE14
U10: LTC3786; QFN-16
U11: 7490220123
U12: MAX4080SAUA+; uMAX-8
U13: TLV70327DBVR; SOT-23-5

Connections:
+48V: C21.1, C22.1, C23.1, C24.1, C25.1, C32.1, D5.1 (K), Q8.5 (D), R12.2, R32.2, U12.1 (RS+), U12.2 (VCC)
/3V3_OR: C14.1, D6.1 (K), D7.1 (K), U8.4 (Vin), U8.5 (RUN/SS)
/3V3_SW: C16.2, D2.1 (K), L1.1, U8.3 (SW)
/48V_EN: R13.2, U5.11 (PA0), U10.10 (RUN)
/BOOST: C5.1, D4.1 (K), U10.15 (BOOST)
/BOOST_SW: C5.2, L2.2, Q3.5 (D), Q8.1 (S), Q8.2 (S), Q8.3 (S), U10.1 (SW)
/BOT_GATE: Q3.4 (G), U10.12 (BG)
/CC1_A: J1.A5 (CC1), U1.1, U5.28 (PA8), U5.29 (PA9)
/CC1_B: J2.A5 (CC1), U2.1, U5.38 (PD0), U5.39 (PD1)
/CC2_A: J1.B5 (CC2), U1.2, U5.27 (PB15), U5.32 (PA10)
/CC2_B: J2.B5 (CC2), U2.2, U5.40 (PD2), U5.41 (PD3)
/CPE_1_N: J4.2 (O), U11.3 (D1-)
/CPE_1_P: J4.1 (O/W), U11.2 (D1+)
/CPE_2_N: J4.4 (B), U11.8 (D3+)
/CPE_2_P: J4.3 (G/W), U11.5 (D2+)
/CPE_3_N: J4.6 (G), U11.6 (D2-)
/CPE_3_P: J4.5 (B/W), U11.9 (D3-)
/CPE_4_N: J4.8 (Br), U11.12 (D4-)
/CPE_4_P: J4.7 (Br/W), U11.11 (D4+)
/CURRENT_THRESH: C20.1, R30.2, U10.6 (ITH)
/DIGIPOT_SCL: R2.2, U3.2 (SCL), U4.2 (SCL), U5.47 (PB8)
/DIGIPOT_SDA: R6.2, U3.3 (SDA), U4.3 (SDA), U5.48 (PB9)
/DISHY_48V: D9.1 (K), D10.1 (K), Q5.5 (D), Q7.2 (S), R28.1, R39.2, U11.21 (CX2), U11.24 (CX1)
/DISHY_48V_HIGH: D8.1 (K), Q5.1 (S), Q5.2 (S), Q5.3 (S), R12.1, R38.2, U12.8 (RS-)
/DISHY_CURRENT_SENSE: U5.12 (PA1), U12.5 (OUT)
/DISHY_POWER_EN: Q4.1 (G), R14.2, U5.15 (PA4)
/DISHY_SENSE_EN: Q6.1 (G), R34.2, U5.16 (PA5), U13.3 (EN)
/DISHY_SENSE_HIGH_SIDE: R17.1, R28.2, U5.13 (PA2)
/DISHY_SENSE_LOW_SIDE: R36.1, U5.14 (PA3)
/Dishy_1_N: J5.2 (O), U11.22 (X1-)
/Dishy_1_P: J5.1 (O/W), U11.23 (X1+)
/Dishy_2_N: J5.4 (B), U11.17 (X3+)
/Dishy_2_P: J5.3 (G/W), U11.20 (X2+)
/Dishy_3_N: J5.6 (G), U11.19 (X2-)
/Dishy_3_P: J5.5 (B/W), U11.16 (X3-)
/Dishy_4_N: J5.8 (Br), U11.13 (X4-)
/Dishy_4_P: J5.7 (Br/W), U11.14 (X4+)
/FB: R32.1, R33.2, U10.3 (VFB)
/FREQ: R27.2, U10.9 (FREQ)
/IND_B: R5.2, U5.45 (PB6)
/IND_G: R4.1, U5.44 (PB5)
/IND_R: R3.1, U5.43 (PB4)
/INTVcc: C18.1, D4.2 (A), U10.13 (INTVcc)
/L_HIGH: L2.1, R31.1, U10.5 (SENSE-)
/SHIELD_C: C26.1, J4.S (SHIELD)
/SHIELD_D: C28.1, J5.S (SHIELD)
/SOFT_START: C19.1, U10.7 (SS)
/SWDCLK: J3.5 (SWDCLK), R9.1, U5.36 (PA14-BOOT0)
/SWDIO: J3.6 (SWDIO), U5.35 (PA13)
/TOP_GATE: Q8.4 (G), U10.16 (TG)
/VBUS_A: C4.1, C12.1, D6.2 (A), J1.A4 (VBUS), J1.A9 (VBUS), J1.B4 (VBUS), J1.B9 (VBUS), U6.12 (VBB), U6.13 (VBB)
/VBUS_A_EN: R11.1, U5.23 (PB11), U6.2 (EN)
/VBUS_A_SW: C29.1, C31.1, Q1.1 (S), Q1.2 (S), Q1.3 (S), U6.9 (VOUT), U6.10 (VOUT), U9.1 (IN1)
/VBUS_B: C3.1, C11.1, D7.2 (A), J2.A4 (VBUS), J2.A9 (VBUS), J2.B4 (VBUS), J2.B9 (VBUS), U7.12 (VBB), U7.13 (VBB)
/VBUS_B_EN: R10.1, U5.24 (PB12), U7.2 (EN)
/VBUS_B_SW: C13.1, C30.1, Q2.1 (S), Q2.2 (S), Q2.3 (S), U7.9 (VOUT), U7.10 (VOUT), U9.5 (IN2)
/VBUS_OR: C36.2, Q1.5 (D), Q2.5 (D), R31.2, U9.3 (OUT), U10.4 (SENSE+), U10.14 (VBIAS)
/nRESET: C1.1, J3.2 (nRESET), R1.2, U5.10 (PF2-NRST)
GND: C1.2, C2.2, C3.2, C4.2, C6.2, C7.2, C8.2, C9.2, C10.2, C11.2, C12.2, C13.2, C14.2, C15.2, C17.2, C18.2, C19.2, C20.2, C21.2, C22.2, C23.2, C24.2, C25.2, C26.2, C27.2, C28.2, C29.2, C30.2, C31.2, C32.2, C33.2, C34.2, C35.2, C36.1, D2.2 (A), J1.A1 (GND), J1.A12 (GND), J1.B1 (GND), J1.B12 (GND), J1.S1 (SHIELD), J2.A1 (GND), J2.A12 (GND), J2.B1 (GND), J2.B12 (GND), J2.S1 (SHIELD), J3.3 (GND), Q3.1 (S), Q3.2 (S), Q3.3 (S), Q4.2 (S), Q6.2 (S), R7.2, R8.2, R9.2, R10.2, R11.2, R13.1, R14.1, R16.1, R17.2, R19.1, R20.1, R25.2, R26.1, R27.1, R33.1, R34.1, U1.3, U2.3, U3.5 (GND), U3.6 (L), U3.9 (GND), U4.4 (A0), U4.5 (GND), U4.6 (L), U4.9 (GND), U5.7 (VSS/VSSA), U5.49 (VSS), U6.1 (GND), U6.3 (DIAG_EN), U6.4 (~FAULT), U6.5 (LATCH), U6.15 (GND), U7.1 (GND), U7.3 (DIAG_EN), U7.4 (~FAULT), U7.5 (LATCH), U7.15 (GND), U8.11 (GND), U9.6 (~VDSFLT), U9.7 (GND), U9.8 (SET), U9.9 (MON2), U9.10 (~PWRFLT2), U9.11 (~FUSEFLT2), U9.12 (~FUSEFLT1), U9.13 (~PWRFLT1), U9.14 (MON1), U9.15 (GND), U10.2 (PGOOD), U10.8 (PLLIN/MODE), U10.11 (GND), U10.17 (GND), U11.15 (CX4), U11.18 (CX3), U12.4 (GND), U13.2 (GND)
unnamed: C15.1, R18.1
unnamed: C27.1, R21.2, R22.2, R23.2, R29.2
unnamed: C35.1, R30.1
unnamed: D1.3 (BK), R5.1
unnamed: D1.4 (GK), R4.2
unnamed: D1.1 (RK), R3.2
unnamed: D3.2 (A), R26.2
unnamed: D5.2 (A), R20.2
unnamed: D8.2 (A), Q5.4 (G), R15.2, R38.1
unnamed: D9.2 (A), R16.2
unnamed: D10.2 (A), Q7.1 (G), R35.2, R39.1
unnamed: Q1.4 (G), U9.2 (GATE1)
unnamed: Q2.4 (G), U9.4 (GATE2)
unnamed: Q4.3 (D), R15.1
unnamed: Q6.3 (D), R35.1
unnamed: Q7.3 (D), R36.2, R37.2
unnamed: U3.7 (W), U3.8 (H), U7.7 (ILIM)
unnamed: U4.7 (W), U4.8 (H), U6.7 (ILIM)
unnamed: R8.1, U6.6 (SNS)
unnamed: R7.1, U7.6 (SNS)
unnamed: C16.1, U8.2 (BOOST)
unnamed: R24.1, R25.1, U8.8 (FB)
unnamed: R19.2, U8.10 (Rt)
unnamed: R18.2, U8.9 (Vc)
unnamed: R21.1, U11.1 (CD1)
unnamed: R22.1, U11.4 (CD2)
unnamed: R23.1, U11.7 (CD3)
unnamed: R29.1, U11.10 (CD4)
unnamed: C33.1, R37.1, U13.5 (OUT)

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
